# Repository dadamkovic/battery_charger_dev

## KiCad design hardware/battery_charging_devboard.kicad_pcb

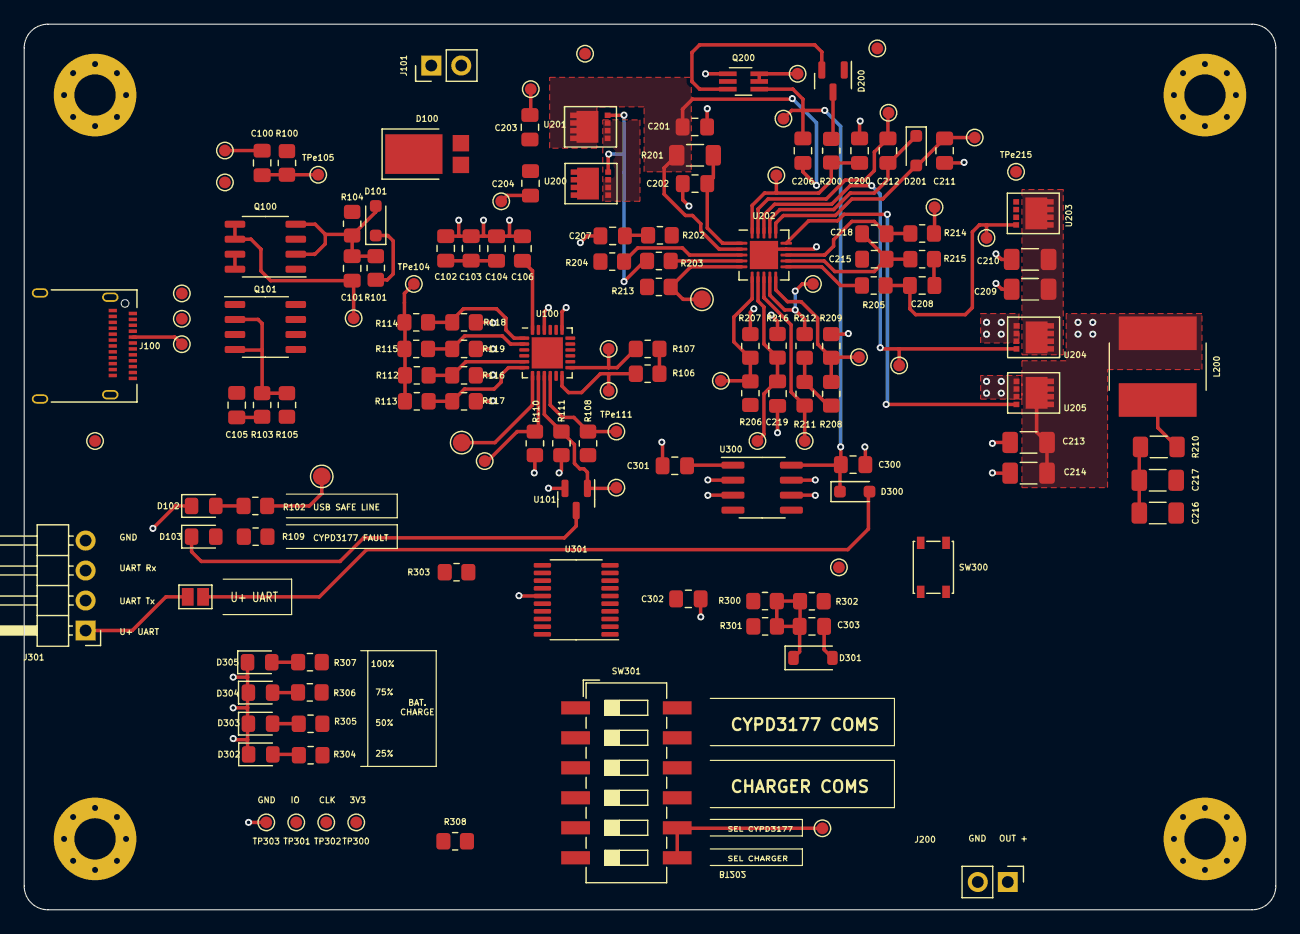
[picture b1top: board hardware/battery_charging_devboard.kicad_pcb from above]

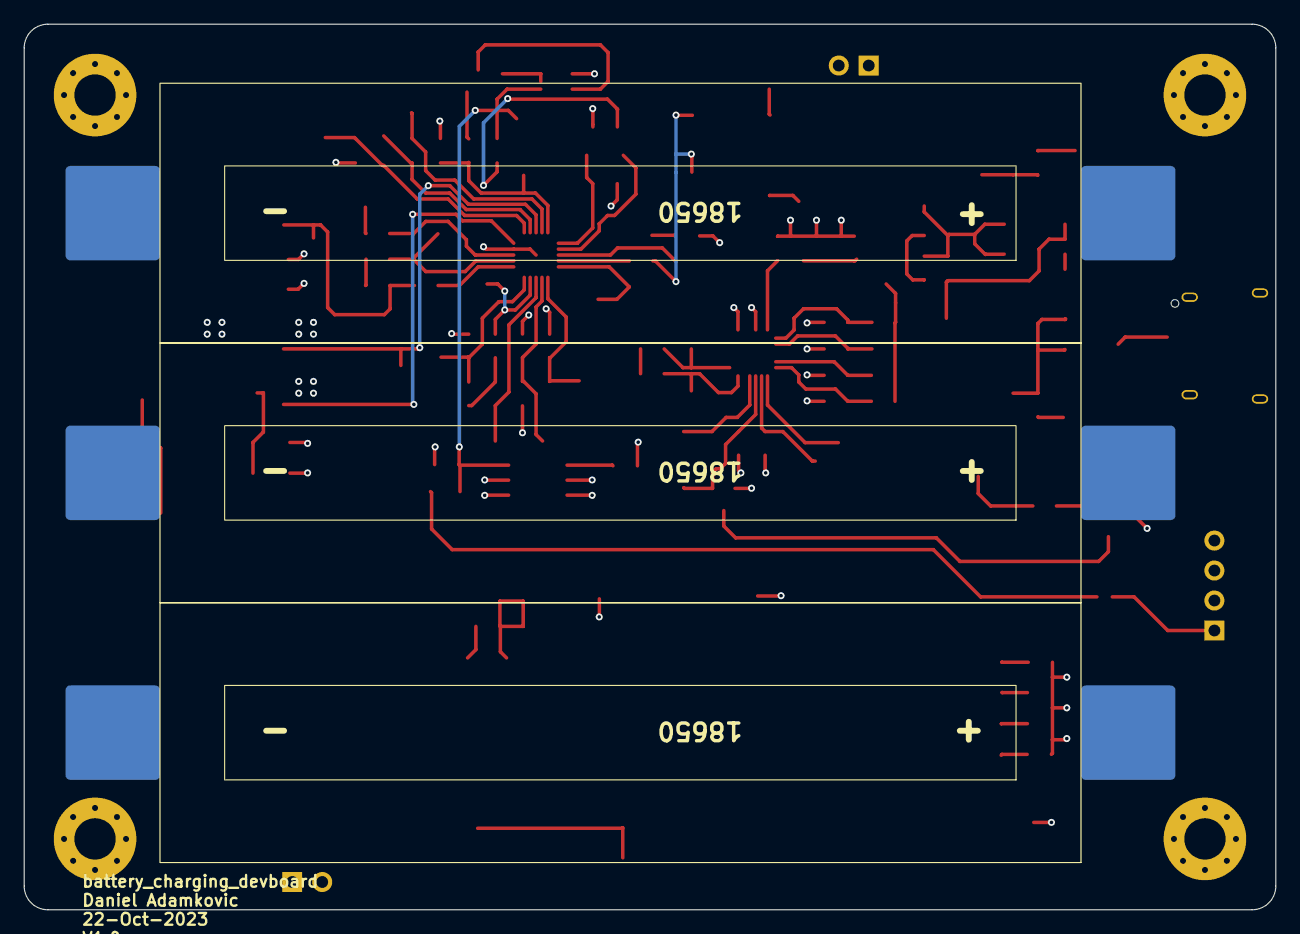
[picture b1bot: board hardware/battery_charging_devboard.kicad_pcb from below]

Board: 4 copper layers, 106.0 x 75.0 mm, 157 parts (3 on the bottom side), 84 nets.

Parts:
B501, B502, B503, B504: MountingHole_Pad; MountingHole_3.5mm_Pad_Via
BT200, BT201, BT202: 18650; Battery_18650
C100, C101, C102, C106: 1u; C_0805_2012Metric_Pad1.18x1.45mm_HandSolder
C103, C104, C200, C201, C202, C204, C206, C211, C215, C218, C301, C302, C303: 0.1u; C_0805_2012Metric_Pad1.18x1.45mm_HandSolder
C105: 3.3u; C_0805_2012Metric_Pad1.18x1.45mm_HandSolder
C203: 2200p; C_0805_2012Metric_Pad1.18x1.45mm_HandSolder
C207: 2.2u; C_0805_2012Metric_Pad1.18x1.45mm_HandSolder
C208: 0.01u; C_0805_2012Metric_Pad1.18x1.45mm_HandSolder
C209, C210, C213, C214, C216, C217: 10u; C_1206_3216Metric_Pad1.33x1.80mm_HandSolder
C212: 0.047u; C_0805_2012Metric_Pad1.18x1.45mm_HandSolder
C219: 100p; C_0805_2012Metric_Pad1.18x1.45mm_HandSolder
C300: 0.33u; C_0805_2012Metric_Pad1.18x1.45mm_HandSolder
D100: SBR8M; D_PowerDI-5
D101, D201, D300: BAT54WS; D_SOD-323_HandSoldering
D102, D103, D302, D303, D304, D305: LED; LED_0805_2012Metric_Pad1.15x1.40mm_HandSolder
D200: BAT54C; SOT-23
D301: MMSZ4684-TP; D_SOD-123
J100: USB_C_Receptacle_USB2.0; USB_C_Receptacle_Amphenol_12401610E4-2A
J101: Conn_01x02_Male; PinHeader_1x02_P2.54mm_Vertical
J200: OUT_SUP; PinHeader_1x02_P2.54mm_Vertical
J300: UART_SUPP; SolderJumper-2_P1.3mm_Open_Pad1.0x1.5mm
J301: UART_CONN; PinHeader_1x04_P2.54mm_Horizontal
L200: 4.7u; L_Bourns_SRN8040TA
Q100, Q101: DMP3036SSD; SO-8_3.9x4.9mm_P1.27mm
Q200: MUN5335DW1T2G; SOT-363_SC-70-6_Handsoldering
R100, R211, R212, R213, R302: 10k; R_0805_2012Metric_Pad1.20x1.40mm_HandSolder
R101, R103: 49.9k; R_0805_2012Metric_Pad1.20x1.40mm_HandSolder
R102, R109, R301, R303, R308: 2k; R_0805_2012Metric_Pad1.20x1.40mm_HandSolder
R104, R105: 1k; R_0805_2012Metric_Pad1.20x1.40mm_HandSolder
R106, R107: 2.2k; R_0805_2012Metric_Pad1.20x1.40mm_HandSolder
R108: 4.7K; R_0805_2012Metric_Pad1.20x1.40mm_HandSolder
R110, R112, R114, R116, R117, R118, R119: 5.1k; R_0805_2012Metric_Pad1.20x1.40mm_HandSolder
R111, R209, R216: 50k; R_0805_2012Metric_Pad1.20x1.40mm_HandSolder
R113: N/A; R_0805_2012Metric_Pad1.20x1.40mm_HandSolder
R115: 0k; R_0805_2012Metric_Pad1.20x1.40mm_HandSolder
R200, R214, R215: 10; R_0805_2012Metric_Pad1.20x1.40mm_HandSolder
R201, R210: 10m; R_1206_3216Metric_Pad1.30x1.75mm_HandSolder
R202: 2; R_0805_2012Metric_Pad1.20x1.40mm_HandSolder
R203, R204, R205: 4k; R_0805_2012Metric_Pad1.20x1.40mm_HandSolder
R206: 430k; R_0805_2012Metric_Pad1.20x1.40mm_HandSolder
R207: 66.5k; R_0805_2012Metric_Pad1.20x1.40mm_HandSolder
R208: 316k; R_0805_2012Metric_Pad1.20x1.40mm_HandSolder
R300: 58k; R_0805_2012Metric_Pad1.20x1.40mm_HandSolder
R304, R305, R306, R307: 660; R_0805_2012Metric_Pad1.20x1.40mm_HandSolder
SW300: BAT_IND; SW_SPST_PTS810
SW301: SW_DIP_x06; SW_DIP_SPSTx06_Slide_6.7x16.8mm_W8.61mm_P2.54mm_LowProfile
TP100, TP101: HPI_INT; TestPoint_Pad_D1.5mm
TP200: ACOK_TP; TestPoint_Pad_D1.5mm
TP300: debug_3V3; TestPoint_Pad_D1.0mm
TP301: debug_swdio; TestPoint_Pad_D1.0mm
TP302: debug_swclk; TestPoint_Pad_D1.0mm
TP303: debug_gnd; TestPoint_Pad_D1.0mm
TPe100, TPe101, TPe102, TPe103, TPe104, TPe105, TPe106, TPe107, TPe108, TPe109, TPe110, TPe111, TPe112, TPe113, TPe200, TPe201, TPe202, TPe203, TPe204, TPe206, TPe207, TPe208, TPe209, TPe210, TPe211, TPe212, TPe213, TPe214, TPe215, TPe216, TPe217, TPe218, TPe300, TPe301: TestPoint; TestPoint_Pad_D1.0mm
U100: CYPD3177; QFN-24-1EP_4x4mm_P0.5mm_EP2.65x2.65mm
U101: T2N7002AK; SOT-23
U200, U201, U203, U204, U205: RQ3E100BN; HSMT8
U202: BQ24725A; Texas_S-PVQFN-N20_EP2.4x2.4mm
U300: L78L33_SO8; SOIC-8_3.9x4.9mm_P1.27mm
U301: STM32F042F6Px; TSSOP-20_4.4x6.5mm_P0.65mm

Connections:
/microcontroller/uC_clk: SW301.10, SW301.12, U301.1 (PB8)
/microcontroller/uC_sda: SW301.9, SW301.11, U301.2 (PF0)
/microcontroller/uC_sel_comms: SW301.7, SW301.8, TPe301.1, U301.3 (PF1)
/microcontroller/uC_swdio: TP301.1, U301.19 (PA13)
/microcontroller/uC_uart_rx: J301.3, U301.9 (PA3)
/microcontroller/uC_uart_tx: J301.2, U301.8 (PA2)
/microcontroller/uc_swclk: TP302.1, U301.20 (PA14)
/usb_input/BACKUP_POWER: D100.2 (A), J101.2
/usb_input/CC1: J100.A5 (CC1), TPe108.1, U100.15 (CC1)
/usb_input/CC2: J100.B5 (CC2), TPe109.1, U100.14 (CC2)
/usb_input/VDDD_3V3: C102.1, C103.1, C104.1, R112.1, R113.1, R114.1, R115.1, TPe104.1, U100.23 (VDDD)
GND: B501.1, B502.1, B503.1, B504.1, BT202.2 (-), C102.2, C103.2, C104.2, C105.2, C106.2, C200.1, C201.2, C202.2, C207.1, C209.1, C210.1, C211.2, C213.1, C214.1, C215.2, C216.1, C217.1, C219.1, C300.2, C301.2, C302.2, C303.2, D102.1 (K), D301.2 (A), D302.1 (K), D303.1 (K), D304.1 (K), D305.1 (K), J100.A1 (GND), J100.A12 (GND), J100.B1 (GND), J100.B12 (GND), J100.S1 (SHIELD), J101.1, J200.2, J301.4, Q200.1 (E1), R110.2, R111.1, R116.2, R117.2, R118.2, R119.2, R207.2, R209.2, R216.1, R302.1, R308.1, SW300.1, TP303.1, U100.19 (GND), U100.22 (VSS), U101.2 (S), U202.14 (GND), U202.21 (GND-PAD), U205.1, U205.2, U205.3, U300.2 (GND), U300.3 (GND), U300.6 (GND), U300.7 (GND), U301.15 (VSSA)
HPI_CLK: R107.2, SW301.1, TPe107.1, U100.13 (HPI_SCL)
HPI_SDA: R106.2, SW301.2, TPe110.1, U100.12 (HPI_SDA)
I2C_CLK_CHRG: R212.2, SW301.3, TPe217.1, U202.9 (SCL)
I2C_SDA_CHRG: R211.2, SW301.4, TPe216.1, U202.8 (SDA)
unnamed: BT200.2 (-), BT201.1 (+)
unnamed: BT201.2 (-), BT202.1 (+)
unnamed: C203.2, C204.2, R203.1, TPe206.1, U200.4, U201.4
unnamed: C204.1, R204.1, TPe203.1, U200.1, U200.2, U200.3, U201.1, U201.2, U201.3
unnamed: C207.2, R202.2
unnamed: C208.2, R205.1, TPe207.1, U203.4
unnamed: C100.2, C101.2, D101.2 (A), Q100.2 (G), Q100.4 (G), R100.2, R101.2, R104.1, TPe101.1
unnamed: D101.1 (K), Q100.1 (S), Q100.3 (S), R101.1, TPe100.1
unnamed: D102.2 (A), R102.1
unnamed: D103.2 (A), R109.1
unnamed: D103.1 (K), U101.3 (D)
unnamed: D200.3, R200.1
unnamed: C211.1, D201.2 (A), TPe209.1, U202.16 (REGN)
unnamed: C212.2, D201.1 (K), U202.17 (BTST)
unnamed: C303.1, D301.1 (K), R300.1, R301.2, R302.2, TPe300.1
unnamed: D302.2 (A), R304.2
unnamed: D303.2 (A), R305.2
unnamed: D304.2 (A), R306.2
unnamed: D305.2 (A), R307.2
unnamed: J300.2, J301.1
unnamed: L200.2, R210.2, R214.1, TPe213.1
unnamed: Q101.2 (G), Q101.4 (G), R103.2, R105.1, TPe103.1
unnamed: Q101.1 (S), Q101.3 (S), TPe102.1
unnamed: Q200.5 (B2), Q200.6 (C1), TPe201.1
unnamed: D200.2, Q200.3 (C2), TPe200.1
unnamed: R303.1, SW300.2
unnamed: R308.2, SW301.5
unnamed: R111.2, TPe113.1, U100.9 (FAULT), U101.1 (G)
unnamed: R108.2, TPe111.1, U100.10 (FLIP)
unnamed: TP101.1, U100.7 (HPI_INT)
unnamed: R112.2, R116.1, U100.5 (ISNK_COARSE)
unnamed: R113.2, R117.1, U100.6 (ISNK_FINE)
unnamed: R105.2, U100.4 (SAFE_PWR_EN)
unnamed: R104.2, U100.3 (VBUS_FET_EN)
unnamed: R115.2, R119.1, U100.2 (VBUS_MAX)
unnamed: R114.2, R118.1, U100.1 (VBUS_MIN)
unnamed: C106.1, U100.24 (VCCD)
unnamed: R206.2, R207.1, TPe210.1, U202.6 (ACDET)
unnamed: R203.2, U202.4 (ACDRV)
unnamed: R213.2, TP200.1, U202.5 (ACOK)
unnamed: C201.1, C206.1, R201.2, TPe208.1, U201.5, U202.2 (ACP)
unnamed: R205.2, U202.11 (BATDR)
unnamed: R204.2, U202.3 (CMSRC)
unnamed: TPe212.1, U202.18 (HIDRV), U204.4
unnamed: R208.1, R209.1, TPe211.1, U202.10 (ILIM)
unnamed: U202.15 (LODRV), U205.4
unnamed: C212.1, C213.2, C214.2, L200.1, TPe214.1, U202.19 (PHASE), U204.1, U204.2, U204.3, U205.5
unnamed: C215.1, C218.2, R215.2, U202.12 (SRN)
unnamed: C218.1, R214.2, U202.13 (SRP)
unnamed: C200.2, R200.2, TPe202.1, U202.20 (VCC)
unnamed: R301.1, U301.6 (PA0)
unnamed: R307.1, U301.7 (PA1)
unnamed: R306.1, U301.10 (PA4)
unnamed: R305.1, U301.12 (PA6)
unnamed: R304.1, U301.13 (PA7)
unnamed: R303.2, U301.14 (PB1)
POWER_SYSTEM: C202.1, C206.2, C209.2, C210.2, C300.1, D300.1 (K), J200.1, Q200.4 (E2), R201.1, TPe204.1, U202.1 (ACN), U203.5, U204.5, U300.8 (IN)
UART_SUPP_5V: D300.2 (A), J300.1
USB_C_BUS: C100.1, C105.1, J100.A4 (VBUS), J100.A9 (VBUS), J100.B4 (VBUS), J100.B9 (VBUS), Q100.7 (D), Q100.8 (G), Q101.7 (D), Q101.8 (G), R100.1, R103.1, R109.2, TPe105.1, U100.18 (VBUS_IN)
USB_C_D+: J100.A6 (D+), J100.B6 (D+), U301.18 (PA10/PA12)
USB_C_D-: J100.A7 (D-), J100.B7 (D-), U301.17 (PA9/PA11)
USB_C_GPIO: R110.1, TPe112.1, U100.8 (GPIO_1)
VREG_3V3: C301.1, C302.1, R106.1, R107.1, R108.1, R208.2, R211.1, R212.1, R213.1, TP300.1, U300.1 (OUT), U301.5 (VDDA), U301.16 (VDD)
V_USB_OUT: C101.1, C203.1, D100.1 (K), D200.1, Q100.5 (D), Q100.6 (G), R202.1, R206.1, TPe106.1, U100.11 (VDC_OUT), U200.5
V_USB_SAFE: Q101.5 (D), Q101.6 (G), R102.2, TP100.1
uC_adc_Icharge: C219.2, R216.2, TPe218.1, U202.7 (IOUT)
uC_adc_battery: BT200.1 (+), C208.1, C216.2, C217.2, R210.1, R215.1, R300.2, TPe215.1, U203.1, U203.2, U203.3
uC_bat_out_en: Q200.2 (B1), U301.11 (PA5)

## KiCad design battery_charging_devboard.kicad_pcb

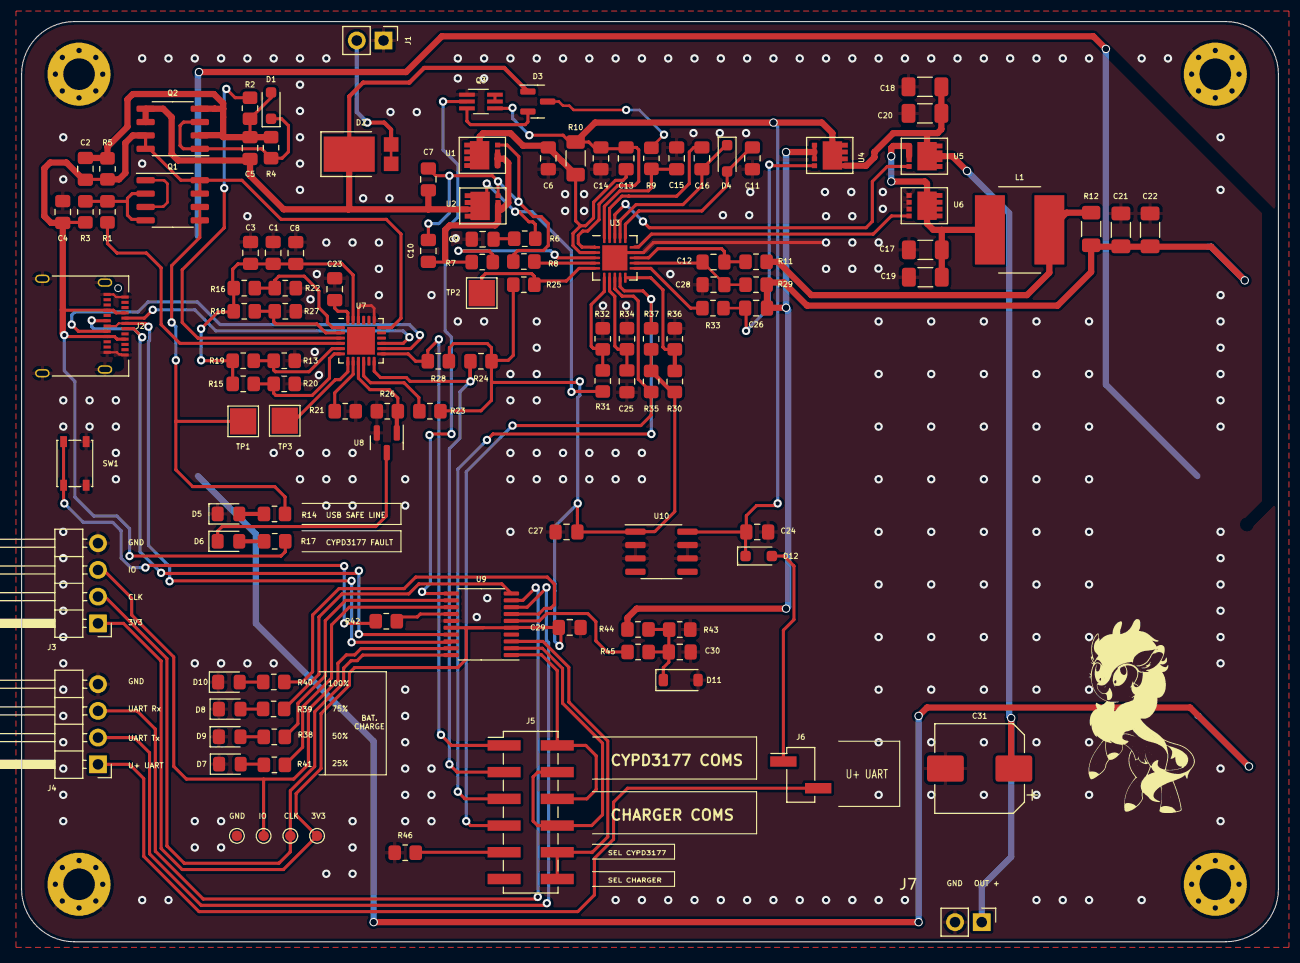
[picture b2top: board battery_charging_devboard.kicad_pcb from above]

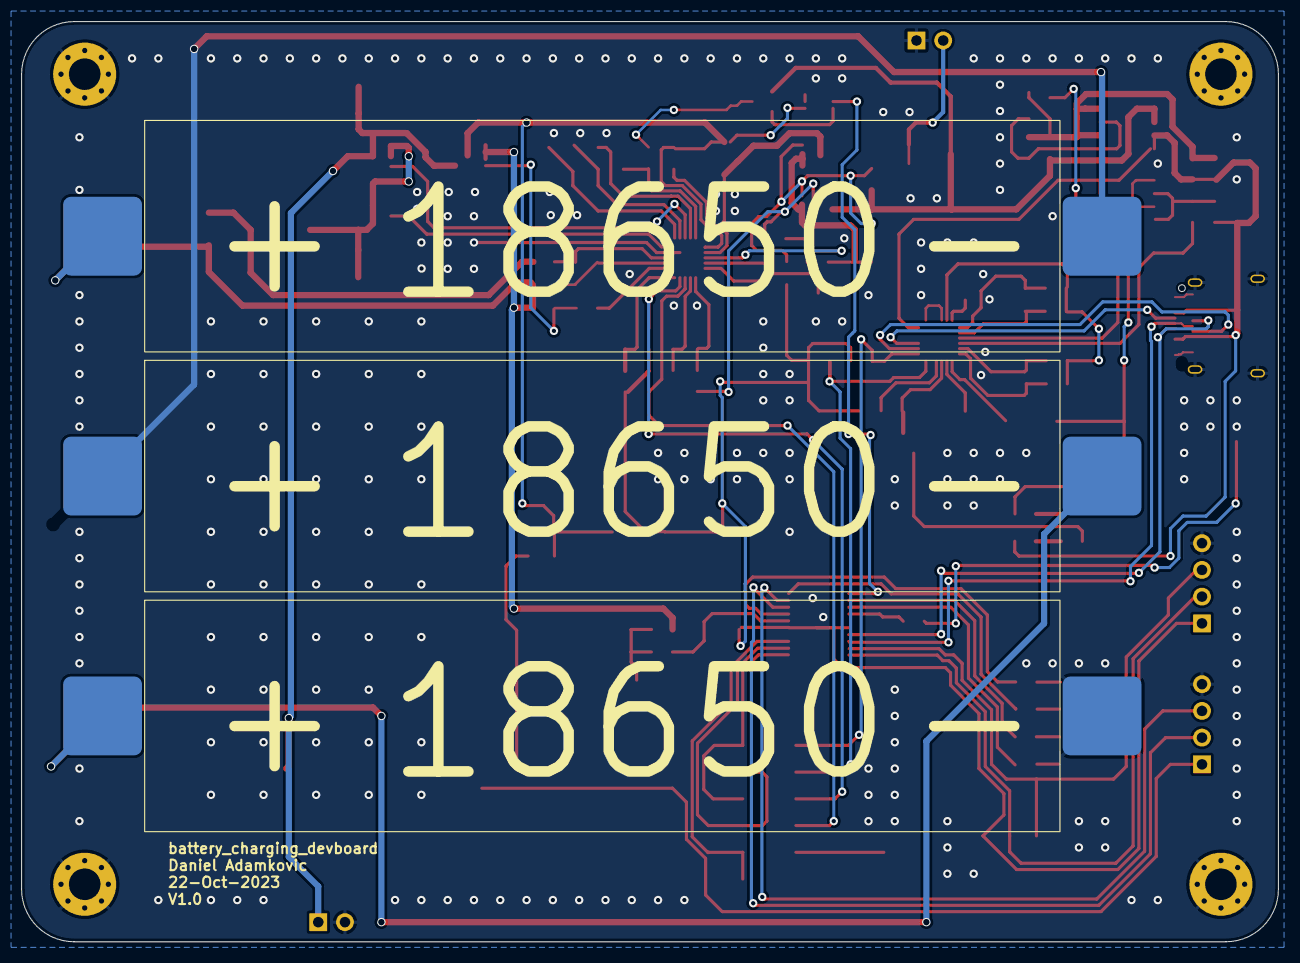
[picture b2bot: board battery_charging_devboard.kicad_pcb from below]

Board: 2 copper layers, 119.5 x 87.5 mm, 121 parts (3 on the bottom side), 85 nets.

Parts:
BT1, BT2, BT3: 18650; Battery_18650
C1, C6, C8, C10, C11, C12, C13, C14, C15, C27, C28, C29, C30: 0.1u; C_0805_2012Metric_Pad1.18x1.45mm_HandSolder
C2, C3, C5, C23: 1u; C_0805_2012Metric_Pad1.18x1.45mm_HandSolder
C4: 3.3u; C_0805_2012Metric_Pad1.18x1.45mm_HandSolder
C7: 2200p; C_0805_2012Metric_Pad1.18x1.45mm_HandSolder
C9: 2.2u; C_0805_2012Metric_Pad1.18x1.45mm_HandSolder
C16: 0.047u; C_0805_2012Metric_Pad1.18x1.45mm_HandSolder
C17, C18, C19, C20, C21, C22: 10u; C_1206_3216Metric_Pad1.33x1.80mm_HandSolder
C24: 0.33u; C_0805_2012Metric_Pad1.18x1.45mm_HandSolder
C25: 100p; C_0805_2012Metric_Pad1.18x1.45mm_HandSolder
C26: 0.01u; C_0805_2012Metric_Pad1.18x1.45mm_HandSolder
C31: 220u; CP_Elec_8x10
D1, D4, D12: BAT54WS; D_SOD-323_HandSoldering
D2: SBR8M; D_PowerDI-5
D3: BAT54C; SOT-23
D5, D6, D7, D8, D9, D10: LED; LED_0805_2012Metric_Pad1.15x1.40mm_HandSolder
D11: MMSZ4684-TP; D_SOD-123
J1: Conn_01x02_Male; PinHeader_1x02_P2.54mm_Vertical
J2: USB_C_Receptacle_USB2.0; USB_C_Receptacle_Amphenol_12401610E4-2A
J3: DEBUG_CONN; PinHeader_1x04_P2.54mm_Horizontal
J4: UART_CONN; PinHeader_1x04_P2.54mm_Horizontal
J5: COMM_SELECT; PinHeader_2x06_P2.54mm_Vertical_SMD
J6: UART_SUPP; PinHeader_1x02_P2.54mm_Vertical_SMD_Pin1Left
J7: OUT_SUP; PinHeader_1x02_P2.54mm_Vertical
L1: 4.7u; L_Bourns_SRN8040TA
Q1, Q2: DMP3036SSD; SO-8_3.9x4.9mm_P1.27mm
Q3: MUN5335DW1T2G; SOT-363_SC-70-6_Handsoldering
R1, R2: 1k; R_0805_2012Metric_Pad1.20x1.40mm_HandSolder
R3, R4: 49.9k; R_0805_2012Metric_Pad1.20x1.40mm_HandSolder
R5, R25, R35, R37, R43: 10k; R_0805_2012Metric_Pad1.20x1.40mm_HandSolder
R6: 2; R_0805_2012Metric_Pad1.20x1.40mm_HandSolder
R7, R8, R33: 4k; R_0805_2012Metric_Pad1.20x1.40mm_HandSolder
R9, R11, R29: 10; R_0805_2012Metric_Pad1.20x1.40mm_HandSolder
R10, R12: 10m; R_1206_3216Metric_Pad1.30x1.75mm_HandSolder
R13, R16, R19, R20, R21, R22, R27: 5.1k; R_0805_2012Metric_Pad1.20x1.40mm_HandSolder
R14, R17, R42, R45, R46: 2k; R_0805_2012Metric_Pad1.20x1.40mm_HandSolder
R15: N/A; R_0805_2012Metric_Pad1.20x1.40mm_HandSolder
R18: 0k; R_0805_2012Metric_Pad1.20x1.40mm_HandSolder
R23: 4.7K; R_0805_2012Metric_Pad1.20x1.40mm_HandSolder
R24, R28: 2.2k; R_0805_2012Metric_Pad1.20x1.40mm_HandSolder
R26, R34, R36: 50k; R_0805_2012Metric_Pad1.20x1.40mm_HandSolder
R30: 316k; R_0805_2012Metric_Pad1.20x1.40mm_HandSolder
R31: 430k; R_0805_2012Metric_Pad1.20x1.40mm_HandSolder
R32: 66.5k; R_0805_2012Metric_Pad1.20x1.40mm_HandSolder
R38, R39, R40, R41: 660; R_0805_2012Metric_Pad1.20x1.40mm_HandSolder
R44: 58k; R_0805_2012Metric_Pad1.20x1.40mm_HandSolder
SW1: BAT_IND; SW_SPST_PTS810
TP1, TP3: HPI_INT; TestPoint_Pad_2.5x2.5mm
TP2: ACOK_TP; TestPoint_Pad_2.5x2.5mm
TP4: debug_gnd; TestPoint_Pad_D1.0mm
TP5: debug_swdio; TestPoint_Pad_D1.0mm
TP6: debug_3V3; TestPoint_Pad_D1.0mm
TP7: debug_swclk; TestPoint_Pad_D1.0mm
U1, U2, U4, U5, U6: RQ3E100BN; HSMT8
U3: BQ24725A; Texas_S-PVQFN-N20_EP2.4x2.4mm
U7: CYPD3177; QFN-24-1EP_4x4mm_P0.5mm_EP2.65x2.65mm
U8: T2N7002AK; SOT-23
U9: STM32F042F6Px; TSSOP-20_4.4x6.5mm_P0.65mm
U10: L78L33_SO8; SOIC-8_3.9x4.9mm_P1.27mm

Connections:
/microcontroller/uC_clk: J5.2, J5.6, U9.1 (PB8)
/microcontroller/uC_sda: J5.4, J5.8, U9.2 (PF0)
/microcontroller/uC_sel_comms: J5.10, J5.12, U9.3 (PF1)
/microcontroller/uC_swdio: J3.3, TP5.1, U9.19 (PA13)
/microcontroller/uC_uart_rx: J4.3, U9.9 (PA3)
/microcontroller/uC_uart_tx: J4.2, U9.8 (PA2)
/microcontroller/uc_swclk: J3.2, TP7.1, U9.20 (PA14)
/usb_input/BACKUP_POWER: D2.2 (A), J1.2
/usb_input/CC1: J2.A5 (CC1), U7.15 (CC1)
/usb_input/CC2: J2.B5 (CC2), U7.14 (CC2)
/usb_input/VDDD_3V3: C1.1, C3.1, C8.1, R15.1, R16.1, R18.1, R19.1, U7.23 (VDDD)
GND: BT3.2 (-), C1.2, C3.2, C4.2, C6.2, C8.2, C9.1, C11.2, C14.2, C15.1, C17.1, C18.1, C19.1, C20.1, C21.1, C22.1, C23.2, C24.2, C25.1, C27.2, C28.2, C29.2, C30.2, C31.2, D5.1 (K), D7.1 (K), D8.1 (K), D9.1 (K), D10.1 (K), D11.2 (A), J1.1, J2.A1 (GND), J2.A12 (GND), J2.B1 (GND), J2.B12 (GND), J2.S1 (SHIELD), J3.4, J4.4, J7.2, Q3.1 (E1), R13.2, R20.2, R21.2, R22.2, R26.1, R27.2, R32.2, R34.1, R36.2, R43.1, R46.1, SW1.1, TP4.1, U3.14 (GND), U3.21 (GND-PAD), U6.1, U6.2, U6.3, U7.19 (GND), U7.22 (VSS), U8.2 (S), U9.15 (VSSA), U10.2 (GND), U10.3 (GND), U10.6 (GND), U10.7 (GND)
HPI_CLK: J5.1, R28.2, U7.13 (HPI_SCL)
HPI_SDA: J5.3, R24.2, U7.12 (HPI_SDA)
I2C_CLK_CHRG: J5.5, R37.2, U3.9 (SCL)
I2C_SDA_CHRG: J5.7, R35.2, U3.8 (SDA)
unnamed: BT1.2 (-), BT2.1 (+)
unnamed: BT2.2 (-), BT3.1 (+)
unnamed: C9.2, R6.2
unnamed: C10.1, R7.1, U1.1, U1.2, U1.3, U2.1, U2.2, U2.3
unnamed: C7.2, C10.2, R8.1, U1.4, U2.4
unnamed: C17.2, C19.2, L1.1, U5.1, U5.2, U5.3, U6.5
unnamed: C26.2, R33.1, U4.4
unnamed: C2.2, C5.2, D1.2 (A), Q2.2 (G), Q2.4 (G), R2.1, R4.2, R5.2
unnamed: D1.1 (K), Q2.1 (S), Q2.3 (S), R4.1
unnamed: D3.3, R9.1
unnamed: C11.1, D4.2 (A), U3.16 (REGN)
unnamed: C16.2, D4.1 (K), U3.17 (BTST)
unnamed: D5.2 (A), R14.1
unnamed: D6.2 (A), R17.1
unnamed: D6.1 (K), U8.3 (D)
unnamed: D7.2 (A), R41.2
unnamed: D8.2 (A), R39.2
unnamed: D9.2 (A), R38.2
unnamed: D10.2 (A), R40.2
unnamed: C30.1, D11.1 (K), R43.2, R44.1, R45.2
unnamed: J4.1, J6.2
unnamed: J5.9, R46.2
unnamed: L1.2, R11.1, R12.2
unnamed: Q1.2 (G), Q1.4 (G), R1.1, R3.2
unnamed: Q1.1 (S), Q1.3 (S)
unnamed: Q3.5 (B2), Q3.6 (C1)
unnamed: D3.2, Q3.3 (C2)
unnamed: R42.1, SW1.2
unnamed: R31.2, R32.1, U3.6 (ACDET)
unnamed: R8.2, U3.4 (ACDRV)
unnamed: R25.2, TP2.1, U3.5 (ACOK)
unnamed: C6.1, C13.1, R10.2, U1.5, U3.2 (ACP)
unnamed: R33.2, U3.11 (BATDR)
unnamed: R7.2, U3.3 (CMSRC)
unnamed: U3.18 (HIDRV), U5.4
unnamed: R30.1, R36.1, U3.10 (ILIM)
unnamed: U3.15 (LODRV), U6.4
unnamed: C16.1, U3.19 (PHASE)
unnamed: C12.2, C28.1, R29.2, U3.12 (SRN)
unnamed: C12.1, R11.2, U3.13 (SRP)
unnamed: C15.2, R9.2, U3.20 (VCC)
unnamed: R26.2, U7.9 (FAULT), U8.1 (G)
unnamed: R23.2, U7.10 (FLIP)
unnamed: TP3.1, U7.7 (HPI_INT)
unnamed: R13.1, R19.2, U7.5 (ISNK_COARSE)
unnamed: R15.2, R20.1, U7.6 (ISNK_FINE)
unnamed: R1.2, U7.4 (SAFE_PWR_EN)
unnamed: R2.2, U7.3 (VBUS_FET_EN)
unnamed: R18.2, R27.1, U7.2 (VBUS_MAX)
unnamed: R16.2, R22.1, U7.1 (VBUS_MIN)
unnamed: C23.1, U7.24 (VCCD)
unnamed: R45.1, U9.6 (PA0)
unnamed: R40.1, U9.7 (PA1)
unnamed: R39.1, U9.10 (PA4)
unnamed: R38.1, U9.12 (PA6)
unnamed: R41.1, U9.13 (PA7)
unnamed: R42.2, U9.14 (PB1)
POWER_SYSTEM: C13.2, C14.1, C18.2, C20.2, C24.1, C31.1, D12.1 (K), J7.1, Q3.4 (E2), R10.1, U3.1 (ACN), U4.5, U5.5, U10.8 (IN)
UART_SUPP_5V: D12.2 (A), J6.1
USB_C_BUS: C2.1, C4.1, J2.A4 (VBUS), J2.A9 (VBUS), J2.B4 (VBUS), J2.B9 (VBUS), Q1.7 (D), Q1.8 (G), Q2.7 (D), Q2.8 (G), R3.1, R5.1, R17.2, U7.18 (VBUS_IN)
USB_C_D+: J2.A6 (D+), J2.B6 (D+), U9.18 (PA10/PA12)
USB_C_D-: J2.A7 (D-), J2.B7 (D-), U9.17 (PA9/PA11)
USB_C_GPIO: R21.1, U7.8 (GPIO_1)
VREG_3V3: C27.1, C29.1, J3.1, R23.1, R24.1, R25.1, R28.1, R30.2, R35.1, R37.1, TP6.1, U9.5 (VDDA), U9.16 (VDD), U10.1 (OUT)
V_USB_OUT: C5.1, C7.1, D2.1 (K), D3.1, Q2.5 (D), Q2.6 (G), R6.1, R31.1, U2.5
V_USB_SAFE: Q1.5 (D), Q1.6 (G), R14.2, TP1.1
uC_adc_Icharge: C25.2, R34.2, U3.7 (IOUT)
uC_adc_battery: BT1.1 (+), C21.2, C22.2, C26.1, R12.1, R29.1, R44.2, U4.1, U4.2, U4.3
uC_bat_out_en: Q3.2 (B1), U9.11 (PA5)

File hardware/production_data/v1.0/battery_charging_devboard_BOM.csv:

"Reference","Value","Footprint","Datasheet","Cost","Price","Source","Vendor","Qty"
"BT1-BT3","18650","User_Battery:Battery_18650","~","","","","","3"
"C1, C6, C8, C10-C15, C27-C30","0.1u","Capacitor_SMD:C_0805_2012Metric_Pad1.18x1.45mm_HandSolder","~","","-- mixed values --","-- mixed values --","","13"
"C2, C3, C5, C23","1u","Capacitor_SMD:C_0805_2012Metric_Pad1.18x1.45mm_HandSolder","~","","","","","4"
"C4","3.3u","Capacitor_SMD:C_0805_2012Metric_Pad1.18x1.45mm_HandSolder","~","","","","","1"
"C7","2200p","Capacitor_SMD:C_0805_2012Metric_Pad1.18x1.45mm_HandSolder","~","","","","","1"
"C9","2.2u","Capacitor_SMD:C_0805_2012Metric_Pad1.18x1.45mm_HandSolder","~","","","","","1"
"C16","0.047u","Capacitor_SMD:C_0805_2012Metric_Pad1.18x1.45mm_HandSolder","~","","","","","1"
"C17-C22","10u","Capacitor_SMD:C_1206_3216Metric_Pad1.33x1.80mm_HandSolder","https://www.mouser.com/datasheet/2/585/MLCC-1837944.pdf","","0.09","","https://www.mouser.com/ProductDetail/Samsung-Electro-Mechani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","6"
"C24","0.33u","Capacitor_SMD:C_0805_2012Metric_Pad1.18x1.45mm_HandSolder","~","","0.065","","https://www.mouser.com/ProductDetail/Samsung-Electro-Mechani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","1"
"C25","100p","Capacitor_SMD:C_0805_2012Metric_Pad1.18x1.45mm_HandSolder","~","","","","","1"
"C26","0.01u","Capacitor_SMD:C_0805_2012Metric_Pad1.18x1.45mm_HandSolder","~","","","","","1"
"C31","220u","Capacitor_SMD:CP_Elec_8x10","https://www.mouser.com/datasheet/2/293/e_uwt-1847810.pdf","","0.286","","https://www.mouser.com/ProductDetail/Nichicon/UWT1V221MNL1GS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","1"
"D1, D4, D12","BAT54WS","Diode_SMD:D_SOD-323_HandSoldering","https://www.mouser.com/datasheet/2/115/DIOD_S_A0004140728_1-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","","0.08","","https://www.mouser.com/ProductDetail/Diodes-Incorporated/BAT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","3"
"D2","SBR8M","Diode_SMD:D_PowerDI-5","https://www.mouser.com/datasheet/2/115/DIOD_S_A0012739531_1-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","0.48","","","https://www.mouser.com/ProductDetail/Diodes-Incorporated/SBR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","1"
"D3","BAT54C","Package_TO_SOT_SMD:SOT-23","http://www.diodes.com/_files/datasheets/ds11005.pdf","","","","","1"
"D5-D10","LED","LED_SMD:LED_0805_2012Metric_Pad1.15x1.40mm_HandSolder","~","","","","","6"
"D11","MMSZ4684-TP","Diode_SMD:D_SOD-123","~","","0.9","","https://www.mouser.com/ProductDetail/Micro-Commercial-Compon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","1"
"J1","Conn_01x02_Male","Connector_PinHeader_2.54mm:PinHeader_1x02_P2.54mm_Vertical","~","","","","","1"
"J2","USB_C_Receptacle_USB2.0","Connector_USB:USB_C_Receptacle_Amphenol_12401610E4-2A","https://www.usb.org/sites/default/files/documents/usb_type-c.zip","","1.33","","https://www.mouser.com/ProductDetail/Amphenol-Commercial-Pro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","1"
"J3","DEBUG_CONN","Connector_PinHeader_2.54mm:PinHeader_1x04_P2.54mm_Horizontal","~","","","","","1"
"J4","UART_CONN","Connector_PinHeader_2.54mm:PinHeader_1x04_P2.54mm_Horizontal","~","","","","","1"
"J5","COMM_SELECT","Connector_PinHeader_2.54mm:PinHeader_2x06_P2.54mm_Vertical_SMD","~","","","","","1"
"J6","UART_SUPP","Connector_PinHeader_2.54mm:PinHeader_1x02_P2.54mm_Vertical_SMD_Pin1Left","~","","","","","1"
"J7","OUT_SUP","Connector_PinHeader_2.54mm:PinHeader_1x02_P2.54mm_Vertical","~","","","","","1"
"L1","4.7u","Inductor_SMD:L_Bourns_SRN8040TA","https://www.mouser.com/datasheet/2/54/srn8040ta-1391519.pdf","","0.38","","https://www.mouser.com/ProductDetail/Bourns/SRN8040TA-4R7M?q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","1"
"Q1, Q2","DMP3036SSD","Package_SO:SO-8_3.9x4.9mm_P1.27mm","https://www.diodes.com/assets/Datasheets/DMP3036SSD.pdf","","0.8","","https://www.mouser.com/ProductDetail/Diodes-Incorporated/DMP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","2"
"Q3","MUN5335DW1T2G","Package_TO_SOT_SMD:SOT-363_SC-70-6_Handsoldering","https://www.mouser.com/datasheet/2/308/1/DTC123JP_D-2311252.pdf","","0.25","","https://www.mouser.com/ProductDetail/onsemi/MUN5335DW1T2G?qs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","1"
"R1, R2","1k","Resistor_SMD:R_0805_2012Metric_Pad1.20x1.40mm_HandSolder","~","","","","","2"
"R3, R4","49.9k","Resistor_SMD:R_0805_2012Metric_Pad1.20x1.40mm_HandSolder","~","","","","","2"
"R5, R25, R35, R37, R43","10k","Resistor_SMD:R_0805_2012Metric_Pad1.20x1.40mm_HandSolder","~","","","","","5"
"R6","2","Resistor_SMD:R_0805_2012Metric_Pad1.20x1.40mm_HandSolder","~","","","","","1"
"R7, R8, R33","4k","Resistor_SMD:R_0805_2012Metric_Pad1.20x1.40mm_HandSolder","~","","","","","3"
"R9, R11, R29","10","Resistor_SMD:R_0805_2012Metric_Pad1.20x1.40mm_HandSolder","~","","","","","3"
"R10, R12","10m","Resistor_SMD:R_1206_3216Metric_Pad1.30x1.75mm_HandSolder","https://www.eaton.com/content/dam/eaton/products/electronic-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","","0.15","","https://www.mouser.com/ProductDetail/Bussmann-Eaton/MFL1206R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","2"
"R13, R16, R19-R22, R27","5.1k","Resistor_SMD:R_0805_2012Metric_Pad1.20x1.40mm_HandSolder","~","","","","","7"
"R14, R17, R42, R45, R46","2k","Resistor_SMD:R_0805_2012Metric_Pad1.20x1.40mm_HandSolder","~","","","","","5"
"R15","N/A","Resistor_SMD:R_0805_2012Metric_Pad1.20x1.40mm_HandSolder","~","","","","","1"
"R18","0k","Resistor_SMD:R_0805_2012Metric_Pad1.20x1.40mm_HandSolder","~","","","","","1"
"R23","4.7K","Resistor_SMD:R_0805_2012Metric_Pad1.20x1.40mm_HandSolder","~","","","","","1"
"R24, R28","2.2k","Resistor_SMD:R_0805_2012Metric_Pad1.20x1.40mm_HandSolder","~","","","","","2"
"R26, R34, R36","50k","Resistor_SMD:R_0805_2012Metric_Pad1.20x1.40mm_HandSolder","~","","","","","3"
"R30","316k","Resistor_SMD:R_0805_2012Metric_Pad1.20x1.40mm_HandSolder","~","","","","","1"
"R31","430k","Resistor_SMD:R_0805_2012Metric_Pad1.20x1.40mm_HandSolder","~","","","","","1"
"R32","66.5k","Resistor_SMD:R_0805_2012Metric_Pad1.20x1.40mm_HandSolder","~","","","","","1"
"R38-R41","660","Resistor_SMD:R_0805_2012Metric_Pad1.20x1.40mm_HandSolder","~","","","","","4"
"R44","58k","Resistor_SMD:R_0805_2012Metric_Pad1.20x1.40mm_HandSolder","~","","","","","1"
"SW1","BAT_IND","Button_Switch_SMD:SW_SPST_PTS810","https://www.mouser.com/datasheet/2/240/pts810-3050339.pdf","","0.3","","https://www.mouser.com/ProductDetail/CK/PTS810SJK250SMTRLFS?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","1"
"TP1, TP3","HPI_INT","TestPoint:TestPoint_Pad_2.5x2.5mm","~","","","","","2"
"TP2","ACOK_TP","TestPoint:TestPoint_Pad_2.5x2.5mm","~","","","","","1"
"TP4","debug_gnd","TestPoint:TestPoint_Pad_D1.0mm","~","","","","","1"
"TP5","debug_swdio","TestPoint:TestPoint_Pad_D1.0mm","~","","","","","1"
"TP6","debug_3V3","TestPoint:TestPoint_Pad_D1.0mm","~","","","","","1"
"TP7","debug_swclk","TestPoint:TestPoint_Pad_D1.0mm","~","","","","","1"
"U1, U2, U4-U6","RQ3E100BN","User_Mosfet:HSMT8","https://www.mouser.com/datasheet/2/348/ROHM_S_A0009370623_1-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","","0.3","","https://www.mouser.com/ProductDetail/ROHM-Semiconductor/RQ3E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","5"
"U3","BQ24725A","Package_DFN_QFN:Texas_S-PVQFN-N20_EP2.4x2.4mm","https://www.ti.com/lit/ds/symlink/bq24725a.pdf?HQS=dis-mous-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","","2.9","","https://www.mouser.com/ProductDetail/Texas-Instruments/BQ247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","1"
"U7","CYPD3177","Package_DFN_QFN:QFN-24-1EP_4x4mm_P0.5mm_EP2.65x2.65mm","https://www.mouser.com/datasheet/2/196/Infineon_EZ_PD_BCR_Da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","","2.2","","https://www.mouser.com/ProductDetail/Infineon-Technologies/C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","1"
"U8","T2N7002AK","Package_TO_SOT_SMD:SOT-23","https://www.mouser.com/datasheet/2/408/T2N7002AK_datasheet_e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","","0.14","","https://www.mouser.com/ProductDetail/Toshiba/T2N7002AKLM?qs=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","1"
"U9","STM32F042F6Px","Package_SO:TSSOP-20_4.4x6.5mm_P0.65mm","https://www.st.com/resource/en/datasheet/stm32f042f6.pdf","","","","","1"
"U10","L78L33_SO8","Package_SO:SOIC-8_3.9x4.9mm_P1.27mm","http://www.st.com/content/ccc/resource/technical/document/da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","","","","","1"

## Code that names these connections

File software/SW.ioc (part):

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Mcu.Name=STM32F042F6Px
Mcu.Package=TSSOP20
Mcu.UserName=STM32F042F6Px
PA0.GPIOParameters=GPIO_Label
PA0.GPIO_Label=BAT_INP_ADC
PA0.Mode=IN0
PA0.Signal=ADC_IN0
PA1.GPIOParameters=GPIO_Label
PA1.GPIO_Label=LED4_OUT
PA1.Signal=GPIO_Output
PA13.Mode=Serial_Wire
PA13.Signal=SYS_SWDIO
PA14.Mode=Serial_Wire
PA14.Signal=SYS_SWCLK
PA4.GPIOParameters=GPIO_Label
PA4.GPIO_Label=LED3_OUT
PA4.Signal=GPIO_Output
PA5.GPIOParameters=GPIO_Label
PA5.GPIO_Label=BAT_EN_OUT
PA5.Signal=GPIO_Output
PA6.GPIOParameters=GPIO_Label
PA6.GPIO_Label=LED2_OUT
PA6.Signal=GPIO_Output
PA7.GPIOParameters=GPIO_Label
PA7.GPIO_Label=LED1_OUT
PA7.Signal=GPIO_Output
PB1.GPIOParameters=GPIO_PuPd,GPIO_Label
PB1.GPIO_Label=BUT1_INP
PB1.GPIO_PuPd=GPIO_PULLUP
PB1.Signal=GPIO_Input
PB8.Mode=I2C
PB8.Signal=I2C1_SCL
PF0-OSC_IN.Mode=I2C
PF0-OSC_IN.Signal=I2C1_SDA
PF1-OSC_OUT.GPIOParameters=GPIO_PuPd,GPIO_Label
PF1-OSC_OUT.GPIO_Label=SEL_COMS_INP
PF1-OSC_OUT.GPIO_PuPd=GPIO_PULLUP
PF1-OSC_OUT.Signal=GPIO_Input
RCC.SYSCLKFreq_VALUE=16000000
RCC.SYSCLKSource=RCC_SYSCLKSOURCE_PLLCLK
board=custom

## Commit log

2023-10-03 Incomplete schematic, added bat charging and PD negotiation.
2023-10-03 Fixed gitignore
2023-10-04 Added microcontroller stage. Need to fix the supply routing to power from battery.
2023-10-15 Schematic completed. Started routing.
2023-10-22 Re-reouting the USB C CCX lines
2024-02-18 Restructured repo
2024-06-29 Continuing routing
